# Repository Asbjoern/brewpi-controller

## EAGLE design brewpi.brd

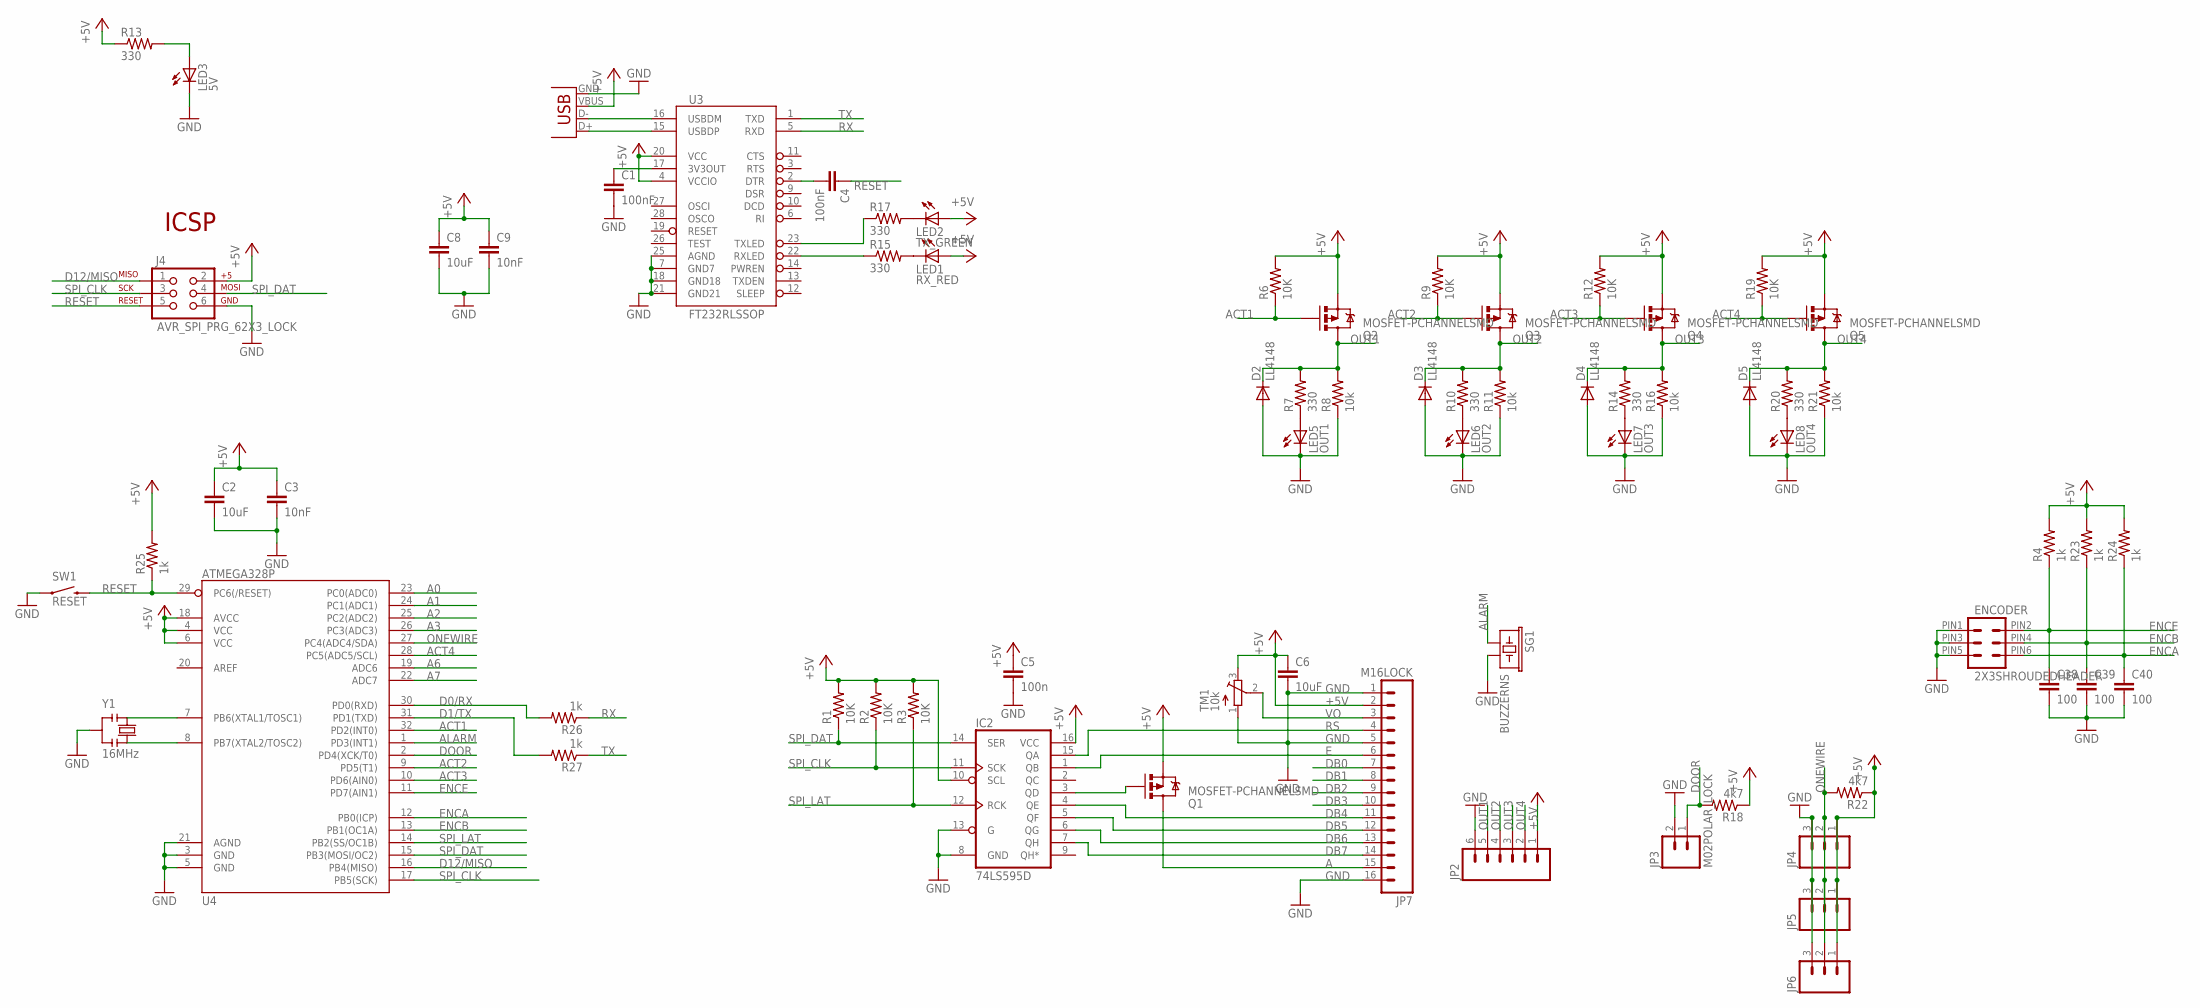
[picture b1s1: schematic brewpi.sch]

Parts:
C1, C4: 100nF; 0603-CAP
C2, C6, C8: 10uF; 0603-CAP
C3, C9: 10nF; 0603-CAP
C5: 100n; 0603-CAP
C38, C39, C40: 100; 0603-CAP
D2, D3, D4, D5: LL4148; MLL34
ENCODER: 2X3SHROUDEDHEADER
IC2: 74LS595D; SO16
J4: AVR_SPI_PRG_62X3_LOCK; 2X3_LOCK
JP1: USBSMD; USB-MINIB
JP2: M06POLAR_LOCK; MOLEX-1X6_LOCK
JP3: M02POLAR_LOCK; MOLEX-1X2_LOCK
JP4, JP5, JP6: M03POLAR_LOCK; MOLEX-1X3_LOCK
JP7: M16LOCK; 1X16_LOCK
LED1: RX_RED; LED-0603
LED2: TX_GREEN; LED-0603
LED3: 5V; LED-0603
LED5: OUT1; LED-0603
LED6: OUT2; LED-0603
LED7: OUT3; LED-0603
LED8: OUT4; LED-0603
Q1, Q2, Q3, Q4, Q5: MOSFET-PCHANNELSMD; SOT23-3
R1, R2, R3, R6, R9, R12, R19: 10K; 0603-RES
R4, R23, R24: 1k; R0603
R7, R10, R13, R14, R15, R17, R20: 330; 0603-RES
R8, R11, R16, R21: 10k; 0603-RES
R18, R22: 4k7; 0603-RES
R25, R26, R27: 1k; 0603-RES
SG1: BUZZERNS; BUZZER-12MM-NS
SW1: RESET; TACTILE_SWITCH_TALL
TM1: 10k; TC33X
U3: FT232RLSSOP; SSOP28DB
U4: ATMEGA328P; TQFP32-08
Y1: 16MHz; RESONATOR

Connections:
+5V: C2.1, C3.1, C5.1, C6.1, C8.1, C9.1, IC2.10 (SCL), IC2.16 (VCC), J4.2, JP1.VBUS, JP2.1, JP4.1, JP5.1, JP6.1, JP7.2, LED1.A, LED2.A, Q1.2 (S), Q2.2 (S), Q3.2 (S), Q4.2 (S), Q5.2 (S), R1.2, R2.2, R3.2, R4.2, R6.2, R9.2, R12.2, R13.1, R18.1, R19.2, R22.1, R23.2, R24.2, R25.2, TM1.3 (E), U3.4 (VCCIO), U3.20 (VCC), U4.4 (VCC), U4.6 (VCC), U4.18 (AVCC)
A: JP7.15, Q1.3 (D)
A0: U4.23 (PC0(ADC0))
A1: U4.24 (PC1(ADC1))
A2: U4.25 (PC2(ADC2))
A3: U4.26 (PC3(ADC3))
A6: U4.19 (ADC6)
A7: U4.22 (ADC7)
ACT1: Q2.1 (G), R6.1, U4.32 (PD2(INT0))
ACT2: Q3.1 (G), R9.1, U4.9 (PD5(T1))
ACT3: Q4.1 (G), R12.1, U4.10 (PD6(AIN0))
ACT4: Q5.1 (G), R19.1, U4.28 (PC5(ADC5/SCL))
ALARM: SG1.+ (1), U4.1 (PD3(INT1))
D0/RX: R26.2, U4.30 (PD0(RXD))
D1/TX: R27.2, U4.31 (PD1(TXD))
D12/MISO: J4.1, U4.16 (PB4(MISO))
DB0: JP7.7
DB1: JP7.8
DB2: JP7.9
DB3: JP7.10
DB4: IC2.4 (QE), JP7.11
DB5: IC2.5 (QF), JP7.12
DB6: IC2.6 (QG), JP7.13
DB7: IC2.7 (QH), JP7.14
DOOR: JP3.1, R18.2, U4.2 (PD4(XCK/T0))
D_M: JP1.D-, U3.16 (USBDM)
D_P: JP1.D+, U3.15 (USBDP)
E: IC2.1 (QB), JP7.6
ENCA: C40.1, ENCODER.PIN6 (6), R24.1, U4.12 (PB0(ICP))
ENCB: C39.1, ENCODER.PIN4 (4), R23.1, U4.13 (PB1(OC1A))
ENCE: C38.1, ENCODER.PIN2 (2), R4.1, U4.11 (PD7(AIN1))
GND: C1.2, C2.2, C3.2, C5.2, C6.2, C8.2, C9.2, C38.2, C39.2, C40.2, D2.A, D3.A, D4.A, D5.A, ENCODER.PIN1 (1), ENCODER.PIN3 (3), ENCODER.PIN5 (5), IC2.8 (GND), IC2.13 (G), J4.6, JP1.GND, JP2.6, JP3.2, JP4.3, JP5.3, JP6.3, JP7.1, JP7.5, JP7.16, LED3.C, LED5.C, LED6.C, LED7.C, LED8.C, R8.1, R11.1, R16.1, R21.1, SG1.- (2), SW1.A2 (1), TM1.1 (A), U3.7 (GND7), U3.18 (GND18), U3.21 (GND21), U3.25 (AGND), U4.3 (GND), U4.5 (GND), U4.21 (AGND), Y1.2
unnamed: U4.7 (PB6(XTAL1/TOSC1)), Y1.1
unnamed: U4.8 (PB7(XTAL2/TOSC2)), Y1.3
unnamed: LED3.A, R13.2
unnamed: C4.2, U3.2 (DTR)
unnamed: IC2.3 (QD), Q1.1 (G)
unnamed: LED1.C, R15.2
unnamed: R15.1, U3.22 (RXLED)
unnamed: R17.1, U3.23 (TXLED)
unnamed: LED2.C, R17.2
unnamed: LED5.A, R7.1
unnamed: LED6.A, R10.1
unnamed: LED7.A, R14.1
unnamed: LED8.A, R20.1
unnamed: C1.1, U3.17 (3V3OUT)
ONEWIRE: JP4.2, JP5.2, JP6.2, R22.2, U4.27 (PC4(ADC4/SDA))
OUT1: D2.C, JP2.5, Q2.3 (D), R7.2, R8.2
OUT2: D3.C, JP2.4, Q3.3 (D), R10.2, R11.2
OUT3: D4.C, JP2.3, Q4.3 (D), R14.2, R16.2
OUT4: D5.C, JP2.2, Q5.3 (D), R20.2, R21.2
RESET: C4.1, J4.5, R25.1, SW1.B2 (2), U4.29 (PC6(/RESET))
RS: IC2.15 (QA), JP7.4
RX: R26.1, U3.5 (RXD)
SPI_CLK: IC2.11 (SCK), J4.3, R2.1, U4.17 (PB5(SCK))
SPI_DAT: IC2.14 (SER), J4.4, R1.1, U4.15 (PB3(MOSI/OC2))
SPI_LAT: IC2.12 (RCK), R3.1, U4.14 (PB2(SS/OC1B))
TX: R27.1, U3.1 (TXD)
VO: JP7.3, TM1.2 (S)

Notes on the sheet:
ICSP

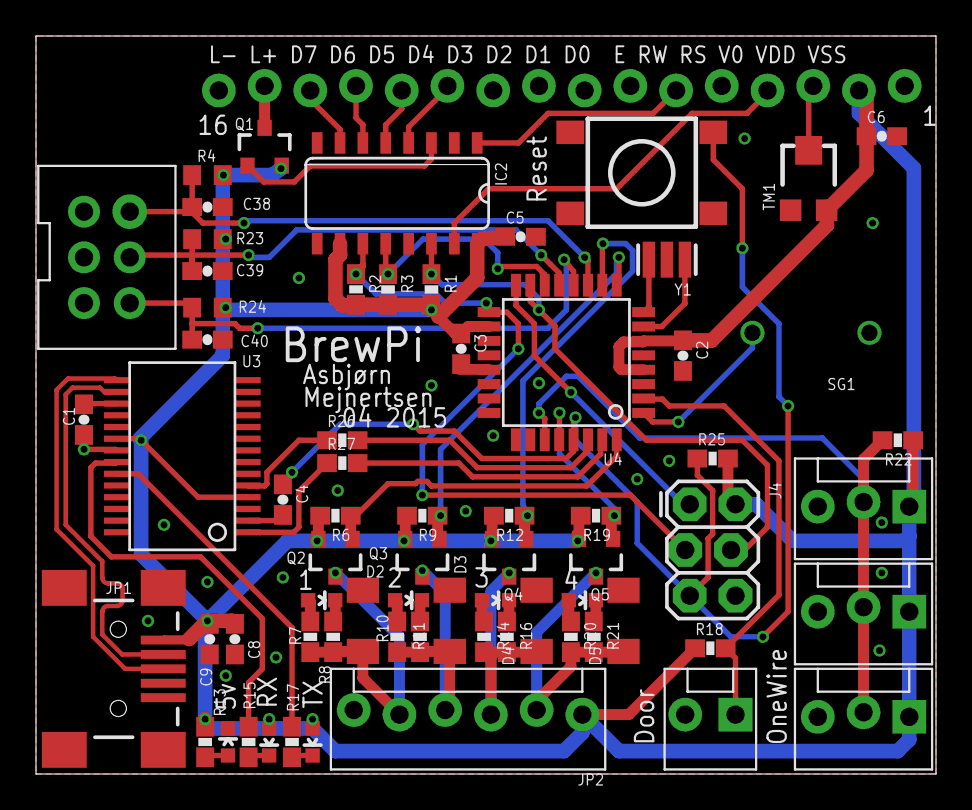
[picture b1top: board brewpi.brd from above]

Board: 4 copper layers, 50.0 x 41.0 mm, 69 parts (1 on the bottom side), 49 nets.

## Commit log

2015-05-08 Added pcb layout Untested!

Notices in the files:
parts and their libraries:
SparkFun-Capacitors: Licensing: CC v3.0 Share-Alike You are welcome to use this library for commercial purposes.
